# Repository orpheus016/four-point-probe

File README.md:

# four-point-probe
Four point probe for semiconductor instrumentation system

## Software: voltage simulation pipeline

This repo includes a modular Python simulation for voltage acquisition with
filters, live plotting, and CSV logging. It is designed to be swapped later with
ADS1256 serial input from Arduino.

## Development

If you plan to change code, start with:

- [CONTRIBUTING.md](CONTRIBUTING.md) for the CI contract, local preflight, and PR checklist.
- [software/scripts/README.md](software/scripts/README.md) for `evaluate`, `integrate`, and the compliance checker.
- [software/README.md](software/README.md) for the software module overview and run examples.
- `CONTRIBUTING.md` also explains how to write new tests under `software/tests/` and run them from the repo root.

### Setup

Install dependencies:

```bash
pip install matplotlib
```

Optional (for future ADS1256 serial input):

```bash
pip install pyserial
```

### Run

From the repo root:

```bash
python -m software.main
```

Example with custom settings:

```bash
python -m software.main --sample-rate 100 --window-seconds 8 --noise 0.0005 --step
```

## Serial protocol and CLI

Hardware integration uses a small text protocol implemented by the Arduino firmware and
managed by `software/command/serial_commander.py`.

Framing markers (exact strings):

- `*STREAM_START` — emitted by the Arduino to mark stream beginning
- `*STREAM_STOP` — emitted by the Arduino to mark stream termination

Control commands sent from host to Arduino (single ASCII characters):

- `R` — reset device
- `C` — start streaming samples
- `s` — stop streaming
- `iN` — set current stage to `N` (e.g. `i2`)

The serial reader expects CSV-style measurement lines containing `voltage,current_mA`.

Common CLI execution examples:

- Replay testbench CSVs and write evaluation results:
	python -m software.scripts.evaluate --input software/output/testbench --out results/

Single backbone on single dataset (example):
	python -m software.scripts.evaluate \
		--input software/output/testbench/stable20mA.csv \
		--backbones baseline \
		--out results/single_baseline_stable20mA
- Run main with hardware ADS1256 on COM5:
	python -m software.main --source serial --port COM5 --baud 115200 --backbone baseline
- Run headless evaluation from Python:
	python -c "from software.scripts.evaluate import main; main(['--input','software/output/testbench'])"

See `software/config/config.py` for all CLI defaults and flags (backbone selection, hysteresis thresholds, plot mode, etc.).

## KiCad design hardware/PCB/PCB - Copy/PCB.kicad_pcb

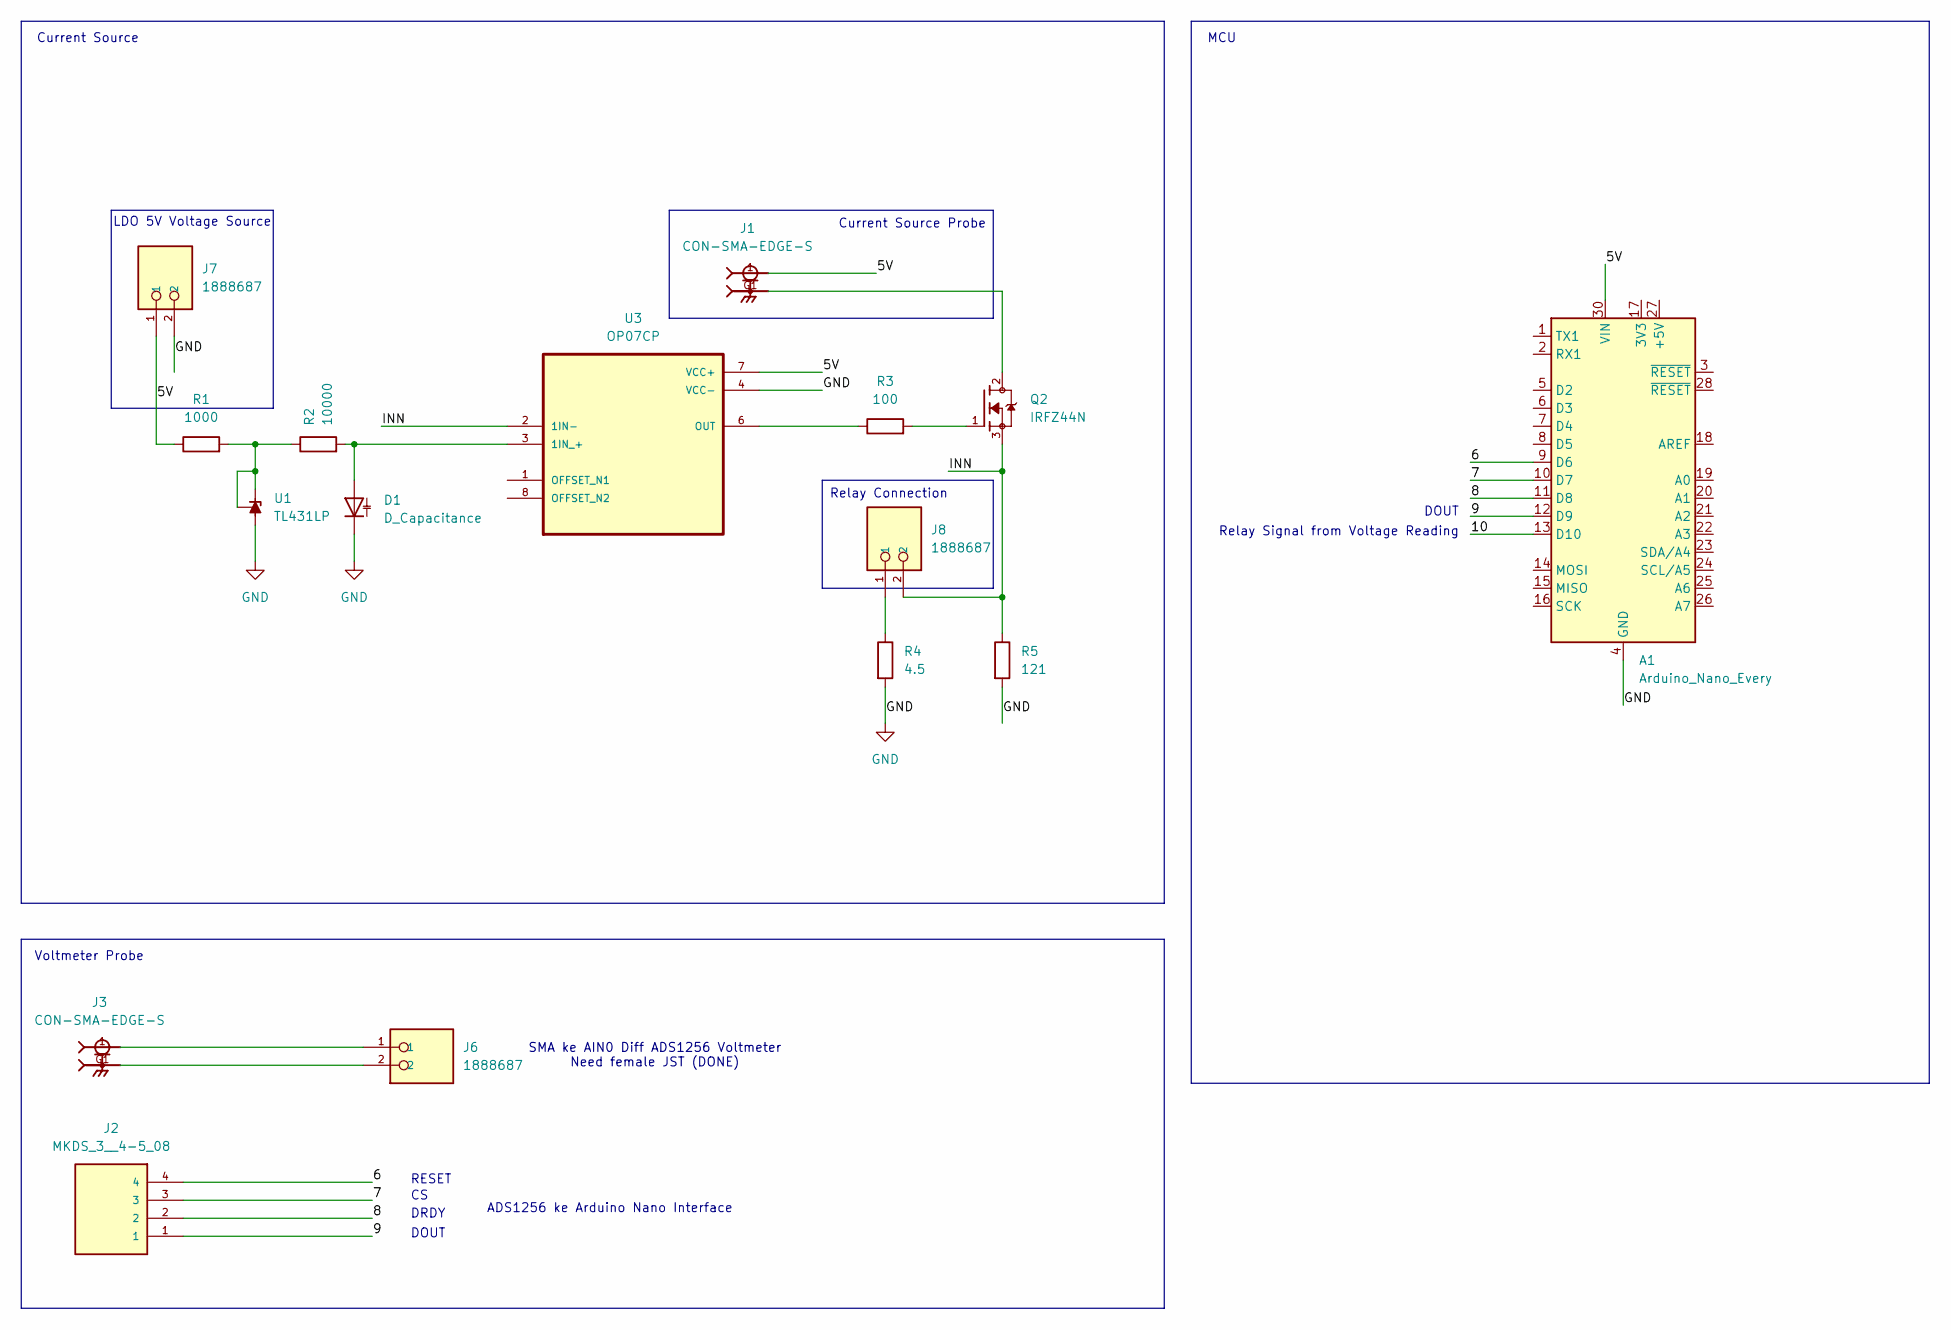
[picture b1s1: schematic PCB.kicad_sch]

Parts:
A1: Arduino_Nano_Every; Arduino_Nano
D1: D_Capacitance; C_Disc_D7.5mm_W5.0mm_P7.50mm
J1, J3: CON-SMA-EDGE-S; RFSOLUTIONS_CON-SMA-EDGE-S; PARTREV 1
J2: MKDS_3__4-5_08; PHOENIX_MKDS_3_4-5_08; PARTREV 11.05.2017
J6, J7, J8: 1888687; PHOENIX_1888687; PARTREV 26.09.2015
Q2: IRFZ44N; TO254P1016X419X2286-3; PARTREV 09/21/10
R1: 1000; R_Axial_DIN0207_L6.3mm_D2.5mm_P10.16mm_Horizontal
R2: 10000; R_Axial_DIN0207_L6.3mm_D2.5mm_P10.16mm_Horizontal
R3: 100; R_Axial_DIN0207_L6.3mm_D2.5mm_P10.16mm_Horizontal
R4: 4.5; R_Axial_DIN0207_L6.3mm_D2.5mm_P10.16mm_Horizontal
R5: 121; R_Axial_DIN0207_L6.3mm_D2.5mm_P10.16mm_Horizontal
U1: TL431LP; TO-92_Inline
U3: OP07CP; DIP794W45P254L959H508Q8

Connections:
/5V: A1.30 (VIN), J1.1, J7.1, R1.1, U3.7 (VCC+)
/6: A1.9 (D6), J2.4
/7: A1.10 (D7), J2.3
/8: A1.11 (D8), J2.2
/9: A1.12 (D9), J2.1
/10: A1.13 (D10)
/INN: J8.2, Q2.3, R5.1, U3.2 (1IN-)
GND: A1.4 (GND), A1.29 (GND), D1.1 (K), J7.2, R4.2, R5.2, U1.2 (A), U3.4 (VCC-)
unnamed: D1.2 (A), R2.2, U3.3 (1IN_+)
unnamed: J1.G1, J1.G2, J1.G3, J1.G4, Q2.2
unnamed: J3.1, J6.1
unnamed: J3.G1, J3.G2, J3.G3, J3.G4, J6.2
unnamed: J8.1, R4.1
unnamed: Q2.1, R3.2
unnamed: R1.2, R2.1, U1.1 (REF), U1.3 (K)
unnamed: R3.1, U3.6 (OUT)

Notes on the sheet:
ADS1256 ke Arduino Nano Interface
DOUT
MCU
LDO 5V Voltage Source
Current Source Probe
Relay Signal from Voltage Reading
DRDY
Relay Connection
Current Source
Voltmeter Probe
SMA ke AIN0 Diff ADS1256 Voltmeter Need female JST (DONE)
RESET

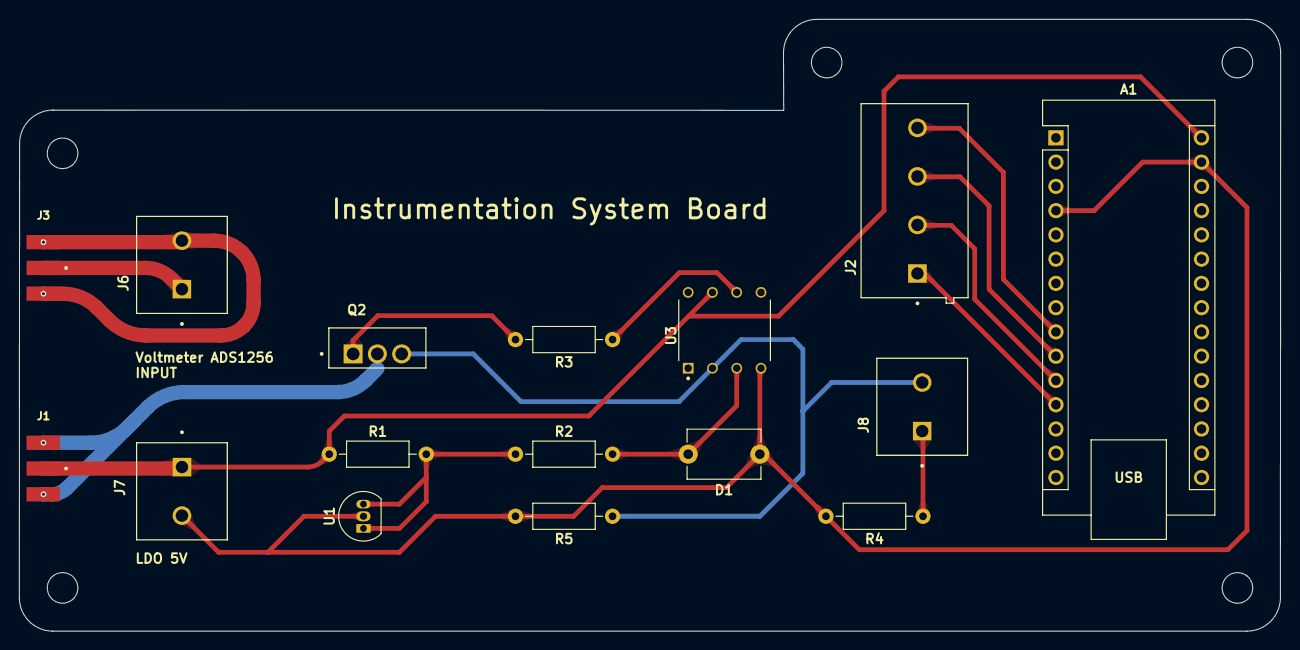
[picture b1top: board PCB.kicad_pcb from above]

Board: 2 copper layers, 132.1 x 64.1 mm, 16 parts (0 on the bottom side), 15 nets.

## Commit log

2026-04-15 add: hardware
2026-04-15 add: software
2026-04-15 add: PCB
2026-05-18 add: voltage snapshot
2026-05-21 add: instrumentation logging
2026-05-22 refactor: move files
2026-05-22 add: gitignore
2026-05-22 refactor: plenty
2026-05-22 add: manual capture
2026-05-22 move: commander
2026-05-23 add: testing
2026-05-23 add: CI
2026-05-23 add: docs
2026-05-23 feat: vi snapshot final on evaluate
2026-05-24 add: CI Compliance
2026-05-24 fix: evaluate
2026-05-24 feat: transient evaluation and animation
2026-05-24 add: running_stat
2026-05-24 add: docs for folder structure
2026-05-24 task: filters and backbones
2026-05-25 fix: real time capture function
2026-05-25 feat: transient plot online
2026-05-25 task: revise the current switching timing and filter
2026-05-26 feat: current switching logic
2026-05-26 task: timing and state diagram
2026-05-26 fix: current switching logic
2026-05-31 feat: real deployment backend
2026-06-05 add: plots
2026-06-06 add: bocd sweep
2026-06-06 add: backbone sweep
2026-06-06 add: signal analysis
2026-06-06 add: algorithm evaluation
2026-06-06 add: temporal robustness
